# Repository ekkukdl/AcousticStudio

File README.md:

# Acoustic Control Studio

2026-10-08 T6 단면 클릭·드래그, 선택/전체 제어점 XYZ 이동, 비동기 궤적 이송과 최신 프레임 큐를 추가했습니다.
`구성 → 제어점`에서 이동 대상·단면·간격을 선택하며, 느린 계산에서는 이전 waypoint를 완료한 뒤 진행합니다.
[사용법·검증·현재 PC 성능](docs/ultraino_t6_result.md)을 확인하세요. 실제 터널 부양·이송 검증은 남아 있습니다.

현재 개발 저장소는 **[ekkukdl/AcousticStudio](https://github.com/ekkukdl/AcousticStudio)** 하나로 통합했습니다. 2026-10-07 기준 `AcousticStudio_ver2`의 코드, 구상도·PCB·Creo 자료 및 로컬 수정 내용을 반영했으며 두 저장소의 커밋 이력을 보존했습니다.

화면은 **보기 → UI → 클래식 / 모던**에서 선택합니다. 두 화면 모두 상단 **보드** 메뉴를 사용합니다. 설계 자료는 [구상도 시작 안내](구상도/START_HERE.md), 최신 32채널 PCB는 [제작 자료 안내](구상도/outputs/panel_8faces_32ch_R1/README.md)를 참고하세요. 통합 범위와 검증 기록은 [저장소 통합 기록](docs/repository_consolidation.md)에 있습니다.

Ultraino 기능 이식은 [작업 계획](docs/ultraino_migration_plan.md)을 기준으로 진행합니다. 현재 대상은 **Creo R2의 8면·8기판·기판당 32송신기, 총 256채널**이며 터널 축은 Z입니다. 기존 배열 좌표와 개발 환경을 재사용하는 범위 및 단계별 완료 조건을 정리했습니다. [입력·환경 점검 결과](docs/ultraino_migration_audit.json)는 현재 로컬 설치 상태의 기록입니다.

Acoustic Control Studio는 초음파 부상(Ultrasonic Levitation) 및 역장 제어(Acoustic Field Control) 연구를 위한 **통합 3D 시뮬레이션 및 하드웨어 제어 소프트웨어**입니다.
이 프로그램은 사용자가 직관적인 3D UI를 통해 센서 배열을 설계하고, 타겟의 위치를 조작하며, 실시간으로 위상(Phase)을 계산하여 하드웨어 보드(아두이노, FPGA 등)로 직접 전송할 수 있는 All-in-One 플랫폼을 제공합니다.

---

## 주요 기능 (Features)
- **3D 대화형 인터페이스 (Interactive 3D UI)**: PyVista 및 PySide6를 기반으로 한 3D 뷰어 제공.
- **다양한 배열 생성**: 터널형, 평면형, 반구형 등 복잡한 센서 배열(Array) 자동 생성 지원.
- **이기종 센서 하이브리드 지원**: 일반 10mm/16mm 초음파 센서와 고출력 랑주뱅(Langevin) 진동자의 혼합 시뮬레이션 지원.
- **실시간 위상 연산 (Real-time Phase Calculation)**: Twin Trap, Vortex Trap 등의 알고리즘을 적용하여 타겟 이동 시 위상을 즉각 재계산하고 색상으로 시각화.
- **하드웨어 연동 (USB Serial)**: 계산된 위상 데이터를 Byte 형식으로 변환하여 실시간으로 외부 제어 보드로 전송.

---

## 사전 설정 및 설치 가이드 (Prerequisites & Installation)

Creo 배열은 `구성 → 배열 형태 → Creo 8면 터널 · 8기판 × 32채널`을 선택하고 `배열 3D 렌더링 생성`으로 추가합니다. 기존 CAD 좌표를 읽으므로 일반 Grid/Spacing 값은 적용되지 않습니다. 위치·회전은 배열 전체에 적용되며, PCB 8개와 프레임 링 2개는 간략 형상으로 표시합니다. [구현 및 검증 기록](docs/ultraino_t1_result.md)을 참고하세요.

`음장 → 공통 음향 모델`에서 무지향, Ultraino sinc, 원형 피스톤을 선택합니다. 기본 개구는 미확정이며 CAD 외경에서 추정하지 않습니다. 방향성 모델에는 유효 음향 개구 반경이 필요하고, 음압은 미보정 상대값입니다. 설정을 바꾼 뒤 위상을 다시 계산하세요. [T2 결과 및 다음 작업](docs/ultraino_t2_result.md)에 데이터 계약과 검증 범위를 정리했습니다.

위상을 계산한 뒤 `음장 → 고정 위상 방사력·복원성 분석`에서 입자 물성, 중력, 평가 범위와 미분 간격을 입력합니다. 현재 송신을 고정한 XYZ 힘·퍼텐셜·복원 곡선과 전체 3×3 복원행렬을 확인하고 분석 JSON을 저장할 수 있습니다. 기본 물성은 예시이며 음압 미보정 상태의 힘은 N* 가정값입니다. 실제 중력 평형·부양 판정은 보류합니다. [T3 결과](docs/ultraino_t3_result.md)를 참고하세요.

다중 제어점을 활성화하고 `음장 → 다중 트랩 설계 (Kinoforms)`를 엽니다. 각 점에 Focus/Twin/Standing Wave, 상대 목표 음압 가중치와 세계 좌표 방향을 지정해 함께 계산합니다. 송신기 이득은 고정하고 위상만 조절하며, 반복 잔차·가중 음압 균일도를 확인한 뒤 `선택 트랩의 고정 위상 분석`으로 T3 복원 부호를 검사할 수 있습니다. `현재 배열에 위상 적용`과 `설계 JSON 저장`을 지원합니다. 음압 균일도는 부양 성공률이 아닙니다. [T4 사용·검증 및 T5 인계](docs/ultraino_t4_result.md)에 재현 방법을 정리했습니다.

`보드 → 채널 보정·맵 및 OFF 프레임…`에서 SW 채널별 위상 오프셋·고정 상대 이득·활성 상태와 후보 채널 맵을 편집하고 JSON/프로젝트로 저장합니다. 보정·맵·양자화·OFF는 실시간 송신과 궤적 내보내기에서 공통 사용합니다. 지원 프로파일의 OFF32와 위상0을 구분하며 Legacy OFF는 거절합니다. 실제 COM 없이 1채널/전체 OFF 프레임을 파일로 확인할 수 있습니다. [T5 사용·검증·T6 인계](docs/ultraino_t5_result.md)를 참고하세요. 실제 펌웨어·배선·파형 검증과 절대 음압 보정은 남아 있습니다.

상단 연산 모드에서 `PyTorch/CUDA: 선택 시 준비`를 선택하면 필요한 CUDA 패키지를 다운로드·확인한 뒤 그 모드를 적용합니다. `도구 → 라이브러리 관리자`의 `PyTorch/CUDA 사용` 체크도 같은 흐름입니다. 첫 준비는 수 GB 다운로드가 필요하며 이후 선택은 바로 전환합니다. 취소·실패는 이전 모드를 유지합니다. [선택 항목 적용 안내](docs/cuda_optional_selection.md)를 참고하세요. 다중 트랩은 복소 행렬 곱만 선택 엔진을 사용하며 작은 문제의 GPU 계산은 복사 비용 때문에 CPU보다 느릴 수 있습니다. [기존 원인·측정 기록](docs/multitrap_cuda_diagnosis.md)을 함께 확인할 수 있습니다.

현재 로컬 개발 환경은 Python 3.13.9이며, 확인한 인터프리터와 의존성은 [이식 계획의 환경 안내](docs/ultraino_migration_plan.md)에 있습니다. 기존 환경을 먼저 확인하고 재사용하세요. 기본 `py`가 선택하는 Python과 앱용 환경은 다를 수 있습니다. 필수 의존성 10개는 `requirements.txt`와 공통 설치 카탈로그에 일치하며, 확인한 버전은 [requirements-tested.txt](requirements-tested.txt)에 기록했습니다. T2는 이미 설치된 SciPy를 재사용했습니다. 아래 신규 설치 예시는 새 머신에 필요한 경우에 사용합니다.

### 1. Python 가상 환경 설정 (선택 사항이나 권장)
```bash
python -m venv venv
# Windows
venv\Scripts\activate
# Mac/Linux
source venv/bin/activate
```

### 2. 필수 라이브러리 설치
프로젝트 루트 폴더에 포함된 `requirements.txt`를 사용하여 의존성 패키지를 한 번에 설치합니다.
```bash
pip install -r requirements.txt
```
**[설치되는 주요 패키지]**
- `PySide6`: GUI 프레임워크
- `pyvista`, `pyvistaqt`, `vtk`: 3D 렌더링 및 기하학 연산 엔진
- `numpy`: 고속 배열 및 위상 수학 연산
- `pyserial`: 하드웨어(USB) 시리얼 통신 모듈

### 3. 프로그램 실행
모든 설치가 완료되었다면, 최상단 경로에서 아래 명령어를 통해 메인 창을 띄울 수 있습니다.
```bash
python main.py
```

---

## 디렉터리 구조 (Directory Structure)
- `src/acousticstudio/`: 애플리케이션의 핵심 소스 코드 (`app.py`, `app_backup.py` 등)
- `main.py`: 프로그램 실행 진입점 (Entry point)
- `docs/`: AI 에이전트 가이드라인 및 프로젝트 진행 상태(`project_status.txt`)가 기록된 문서 폴더
- `archive/temp_scripts/`: 개발 과정에서 생성된 임시 수정 스크립트(수동 코드 인젝션 파일) 모음 보관소
- `requirements.txt`: 의존성 패키지 목록

---

## 주의 사항 (Notes)
- **그래픽 드라이버**: 3D 렌더링 엔진인 VTK/PyVista를 사용하므로, 그래픽 드라이버(OpenGL 호환)가 정상적으로 설치된 환경에서 실행해야 튕김 현상이 발생하지 않습니다.
- **AI 작업 지침**: GPT/Codex를 포함한 코딩 에이전트는 [AGENTS.md](AGENTS.md)의 작업·백업·검증 규칙을 따릅니다. 기존 `GEMINI.md`도 이 공통 지침을 안내합니다. 스킬 점검 내역은 [docs/skill_audit.md](docs/skill_audit.md)에 있습니다.

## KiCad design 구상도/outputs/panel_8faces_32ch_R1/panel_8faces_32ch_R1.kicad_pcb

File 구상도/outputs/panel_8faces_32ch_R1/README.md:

# 8면 터널용 32채널 PCB R1 — KiCad 10

기존 16채널 회로와 배선을 두 전기적 뱅크로 재사용해, 4열 × 8행의 트랜스듀서를 한 장에 배치한 새 설계입니다. 같은 PCB 8장으로 총 256채널을 구성합니다. 기존 설계 파일은 수정하지 않았습니다. 실제 PCB 발주·조립·구동은 수행하지 않았습니다.

## 파일 열기

`panel_8faces_32ch_R1.kicad_pro`를 KiCad 10에서 엽니다. 회로도와 PCB, 프로젝트 로컬 심벌/풋프린트 및 모델이 함께 들어 있습니다. 회로도는 620 × 460 mm 사용자 용지의 단일 시트입니다.

## 이번 시제품의 치수

| 항목 | R1 값 | 의미 |
|---|---:|---|
| PCB | 84 × 224 × 1.6 mm | 2층, 면마다 1장 |
| 발진면 맞은편 거리 | 210 mm | 기존 300 mm에서 축소한 시작점 |
| PCB 앞면의 중심까지 거리 | 117.5 mm | 발진면 거리 + 가정한 소자 높이 12.5 mm |
| 트랜스듀서 | 4 × 8, 지름 16 mm | 기존 풋프린트 사용, 정확한 구매품 확인 필요 |
| 열 중심 간격 | 18 / 22 / 18 mm | 두 기존 배선 셀 사이에 4 mm를 더 확보 |
| 행 중심 간격 | 20 mm | 기존과 동일 |
| 위·아래 고정 여백 | 각각 22 mm | 부품·배선·동박 채움 없는 영역 |
| 고정 구멍 | 4개, 지름 3.2 mm NPTH | (6,11), (78,11), (6,213), (78,213) mm |
| 인접 PCB 앞면 모서리 거리 | 약 12.325 mm | 광학 유효 개구 폭이나 시야각을 뜻하지 않음 |

기판 내부 슬롯은 없습니다. 기판 사이 틈을 남기는 정팔각형 터널 배치이며 외부 카메라와 회전 프레임 자체는 이번 설계 범위 밖입니다. 물체 전체가 보이는 조건은 유지해야 하지만 물체 크기와 촬영 위치가 없어 아직 증명되지 않았습니다.

200 mm가 절대 기준은 아니므로, 기존 셀 배선 유지와 틈 확보를 위해 210 mm를 선택했습니다. 같은 84 mm PCB를 발진면 거리 200 mm로 배치하면 앞면 모서리 거리는 약 8.498 mm로 줄어듭니다. 두 경우 모두 소자 외피는 단순 모델상 충돌하지 않지만 카메라 시야·음향 부상 성능은 별도 검증이 필요합니다. 기판 뒤 부품, 케이블, 프레임은 틈을 더 가릴 수 있습니다.

`parameters.json`은 현재 치수 기록입니다. 생성 스크립트는 보드 폭·길이와 발진면 거리를 조정할 수 있으나 열·행 간격, 소자 높이, 고정 여백 변경을 임의로 자동 배선하지 않습니다. 변경 후 네이티브 파일·간섭·ERC/DRC·제조 파일을 다시 검증해야 합니다. JSON 수치만 바꿔 기존 Gerber를 그대로 사용할 수 없습니다.

## 전기 구성과 연결

32채널을 16채널 A/B 뱅크로 나눕니다. 뱅크 사이에서 PCB 내부로 연결된 공통 전원망은 GND뿐입니다. +5V_A/B, DRV_VDD_A/B, SHIFT/LATCH/ARM_A/B는 각각 외부에서 공급합니다. 같은 공급원이나 클록을 쓰려면 외부 분배가 필요합니다. 한쪽 헤더만 연결하면 다른 뱅크가 자동 동작하지 않습니다.

| 핀 | J1: BANK A 신호 | J2: BANK B 신호 |
|---:|---|---|
|1|GND|GND|
|2|+5V_A|+5V_B|
|3|DATA_A0|DATA_B0|
|4|GND|GND|
|5|DATA_A1|DATA_B1|
|6|GND|GND|
|7|SHIFT_PIN_A|SHIFT_PIN_B|
|8|LATCH_PIN_A|LATCH_PIN_B|
|9|ARM_A|ARM_B|
|10|GND|GND|

J3(A), J4(B) 전원 헤더는 1=DRV_VDD, 2=GND, 3=+5V입니다. 실크와 패드 번호를 기준으로 확인하고 커넥터 뒷면 시점의 좌우를 추측하지 마세요. +5V는 5 V 로직 공급이며 TC4427A의 드라이버 전원 허용 범위는 4.5–18 V입니다. 실제 트랜스듀서의 연속 구동 정격 확인 전 드라이버 전압을 확정하지 않습니다.

ARM 기본 풀다운 → MMBT3904 OFF → 74HCT595 /OE 풀업으로 출력 비활성화합니다. 입력 풀다운으로 TC4427A 입력의 부유를 방지합니다. 전원 안정 후 ARM 비활성 상태에서 4개의 데이터 라인에 값을 시프트하고 래치한 다음 ARM을 활성화하는 순서를 사용합니다. 외부 FPGA와 헤더 배선은 이번에 변경하지 않았습니다.

T1…T32는 행 우선 순서입니다. QA…QH 출력 기준 `channel_map.csv`와 전체 256개 위치 `array_positions_256.json`을 제공합니다. `physical_to_software_channel_map.json`은 문서화한 DATA 순서에 대응하는 후보이며 FPGA의 실제 시프트 비트 방향과 헤더 배선을 확인하기 전 기존 프로그램에 바로 적용하지 않습니다.

## 제작·조립 자료

- `Gerber_R1_PCB_only.zip`: 동박·마스크·실크·페이스트·외곽, PTH/NPTH 드릴 및 Gerber job. PCB 1장 패턴이며 8장 주문 수량은 별도 지정합니다.
- `BOM_ALL.csv`, `BOM_SMT.csv`, `BOM_THT.csv`: 1장 및 8장 수량, 후보 MPN. 1장당 SMT 110개와 THT 38개입니다. M3 고정 나사·프레임·케이블은 포함하지 않습니다.
- `PnP_SMT_KiCad.csv`: KiCad 원본 좌표, mm, Bottom, X 양수/Y 음수. 임의 미러 변환을 하지 않았습니다. 업체의 바닥면 좌표 규약과 반드시 맞춰야 합니다.
- `THT_Placement.csv`: 트랜스듀서·헤더·전해콘덴서 수동 조립 위치. TX 패드1=출력/패드2=GND, 전해콘덴서 패드1=양극입니다.
- `mechanical/panel_board_only.step`: 실제 PCB 외곽·고정 구멍의 STEP. 부품 및 외부 프레임 미포함.
- `mechanical/tunnel_envelope.scad`: 8면 PCB/소자 외피의 치수 모델. 고정 구조 설계용 완성 프레임이 아닙니다.
- `geometry_preview.png`, `assembly_preview.png`, `pcb_top.png`, `pcb_bottom.png`, `schematic_preview.png`: 배치·실제 회로도·배선 미리보기.

PCB 제안 사양은 FR-4, 2층, 1.6 mm, 1 oz 동박이며 제작업체의 실제 공정 사양을 확인해야 합니다. 업체 패널라이징, 리플로우 캐리어, 스텐실 여백, 부품 대체 선정은 이번 패키지에 포함하지 않습니다. THT 트랜스듀서는 안쪽 F면, 구동 부품은 바깥쪽 B면에 배치합니다.

## 검증과 남은 사항

KiCad 10.0.6 ERC 0, DRC 위반 0, 미연결 0, 회로도/PCB 불일치 0. 별도 검증에서 전기 패드 468개(연결 432개/명시 NC 36개), 32개 출력 경로, 256채널 맵, SMT 좌표와 고정 여백을 확인했습니다. 원본 PCB의 SHA-256도 유지되었습니다. GND 비아 92개를 추가했습니다.

기존 프로젝트의 5개 DRC ignore 설정과 ERC ignore 설정은 유지되며 검증 범위는 `DESIGN_REVIEW.md`에 기록했습니다. 제조업체 DFM, 실제 전류·온도·신호 파형·음향 부상과 전체 물체 촬영은 검증되지 않았습니다. 자동 EMC 검토의 귀환 경로 및 외부 케이블 경고가 남아 있어 측정과 필요시 배선 수정이 필요합니다. 자세한 판단과 근거는 `DESIGN_REVIEW.md`, 기계 판정은 `geometry_summary.json`, 원시 검사 결과는 `analysis/`에 있습니다.

## 재생성

프로젝트 루트에서 `구상도/scratch/build_panel32_r1.py`와 `stitch_panel32_r1.py`, `verify_panel32_r1.py`를 KiCad 내장 Python으로 실행합니다. `export_panel32_r1.py`, `render_panel32_r1.py`, `package_panel32_r1.py`는 시스템 Python을 사용합니다. 검증은 ERC/DRC와 XML netlist 내보내기 뒤 수행합니다. 렌더에는 로컬 resvg-py/Pillow, 치수 미리보기에는 numpy/matplotlib이 필요합니다. 생성은 기존 16채널 소스 셀을 읽으므로 소스 폴더가 필요하며 새 설계를 편집한 뒤 생성 스크립트를 다시 실행하면 R1 편집 내용이 덮어써집니다.

## 색상 및 외부 프레임 포함 Creo 모델 R2

[전체 조립체](mechanical/creo32_frame_R2/native/tunnel8_32_r2.asm)는 진녹색 PCB 8장과 회색 상하 팔각 링 2개를 포함합니다. 전체 외형 265×265×224 mm, 기존 PCB 고정 구멍에 맞춘 M3 체결 구멍 및 촬영용 면간 틈을 유지했습니다. [Creo R2 사용안내](mechanical/creo32_frame_R2/사용안내.md)에 치수·파일·검증 범위가 있으며, [모델 ZIP](mechanical/creo32_frame_R2/Creo32_frame_R2_models.zip)에 모든 참조 단품을 포함했습니다. 기판 조립체는 `panel32_r2.asm`, 기판 단품은 `pcb32_r2.prt`, 링 단품은 `ring8_32_r2.prt`입니다. 이전 R1 모델은 보존했습니다.

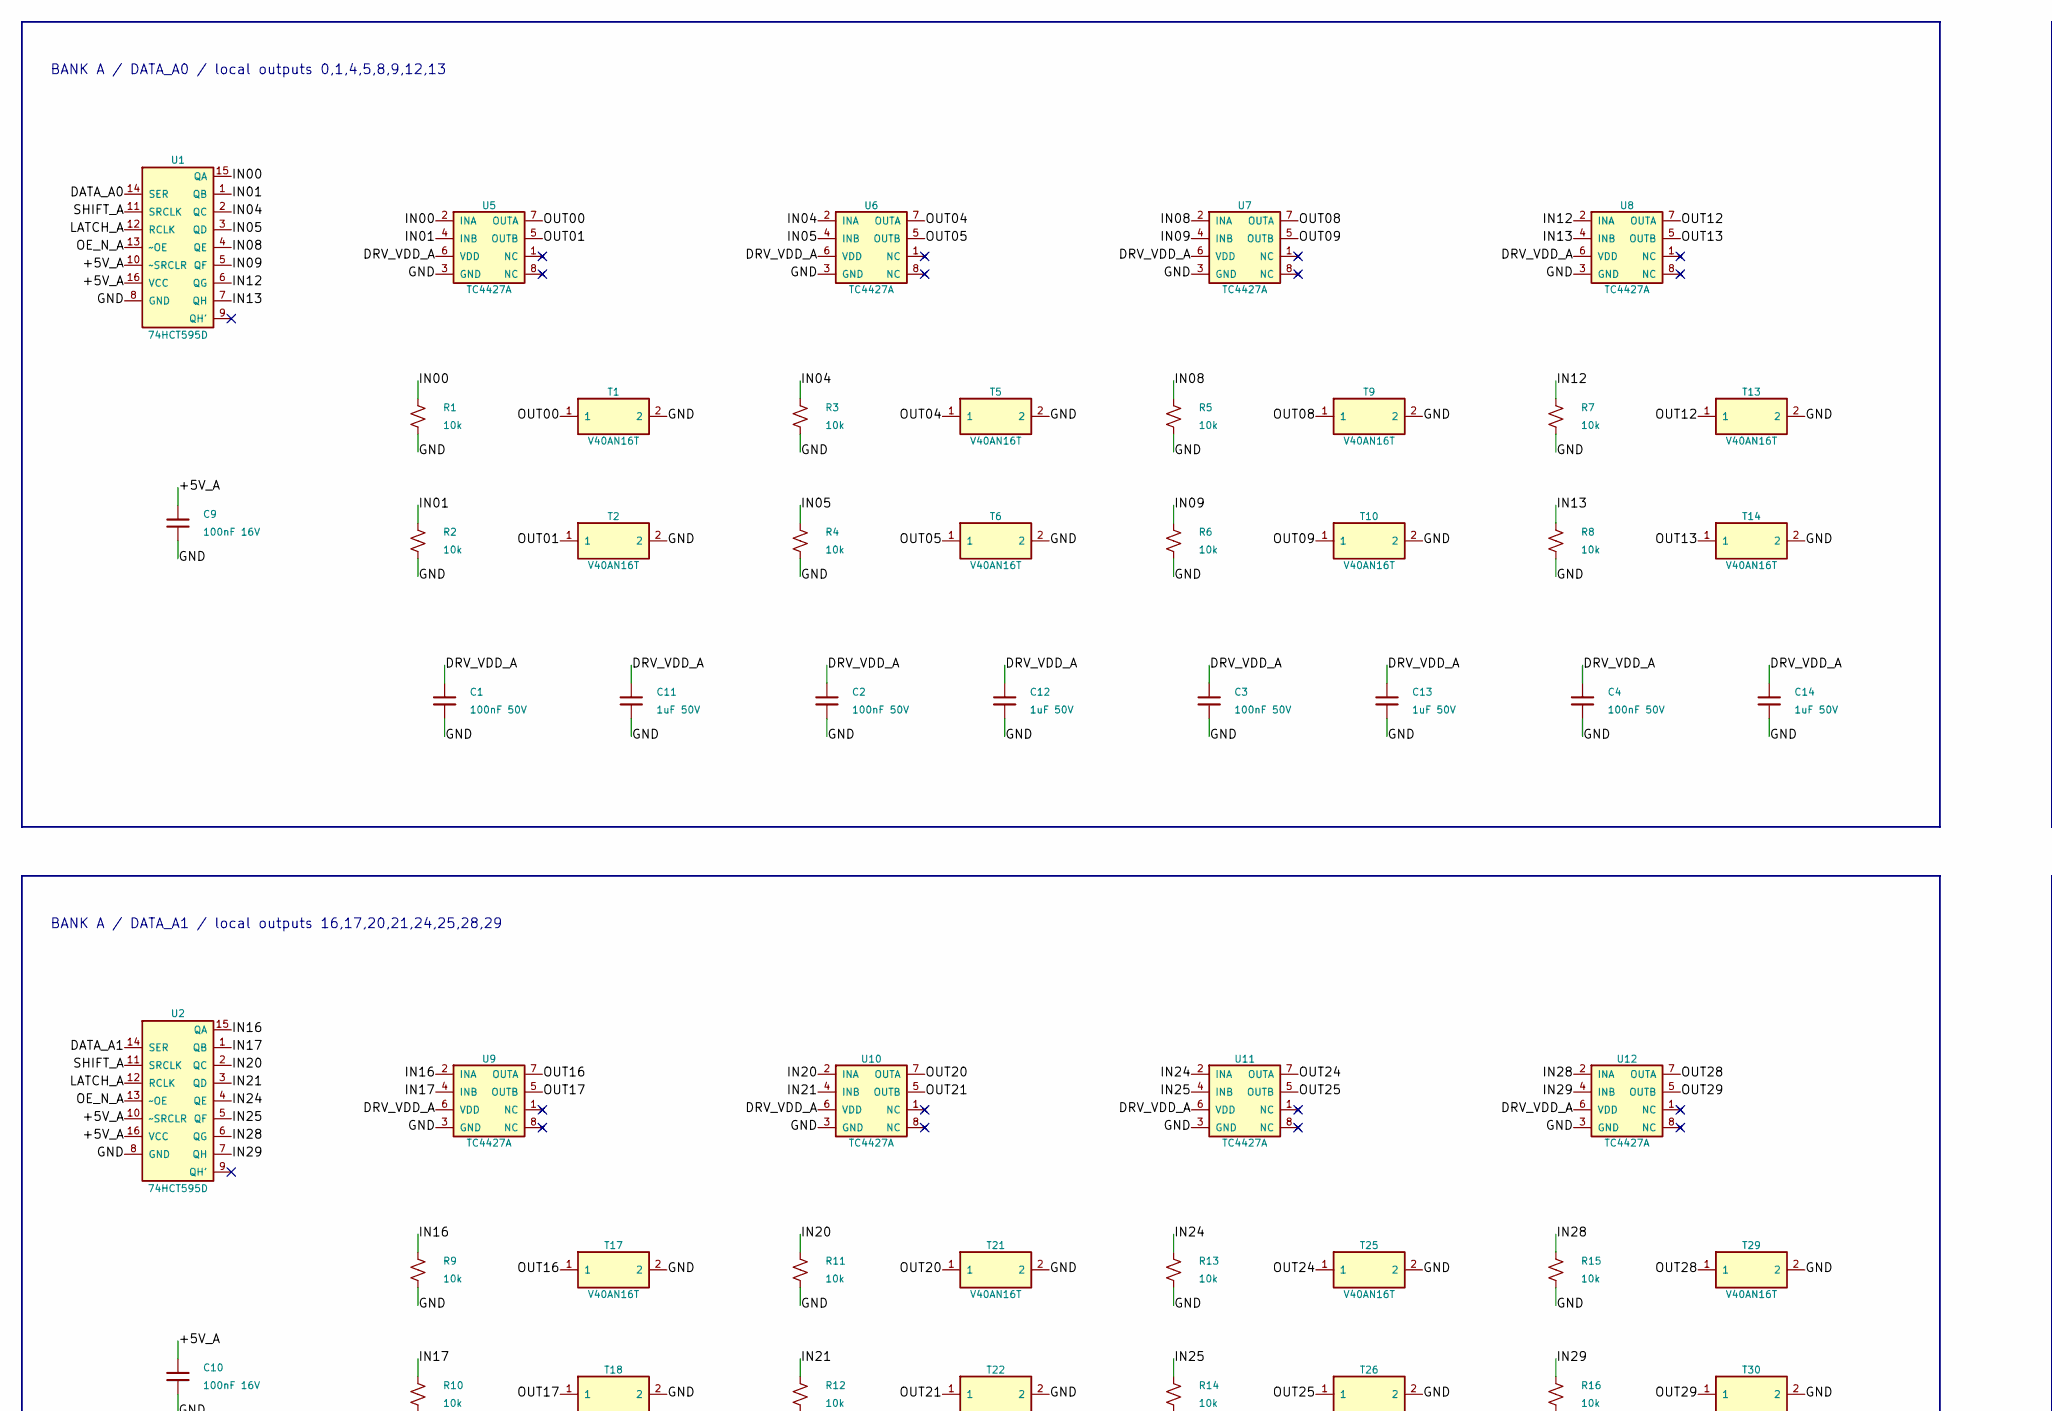
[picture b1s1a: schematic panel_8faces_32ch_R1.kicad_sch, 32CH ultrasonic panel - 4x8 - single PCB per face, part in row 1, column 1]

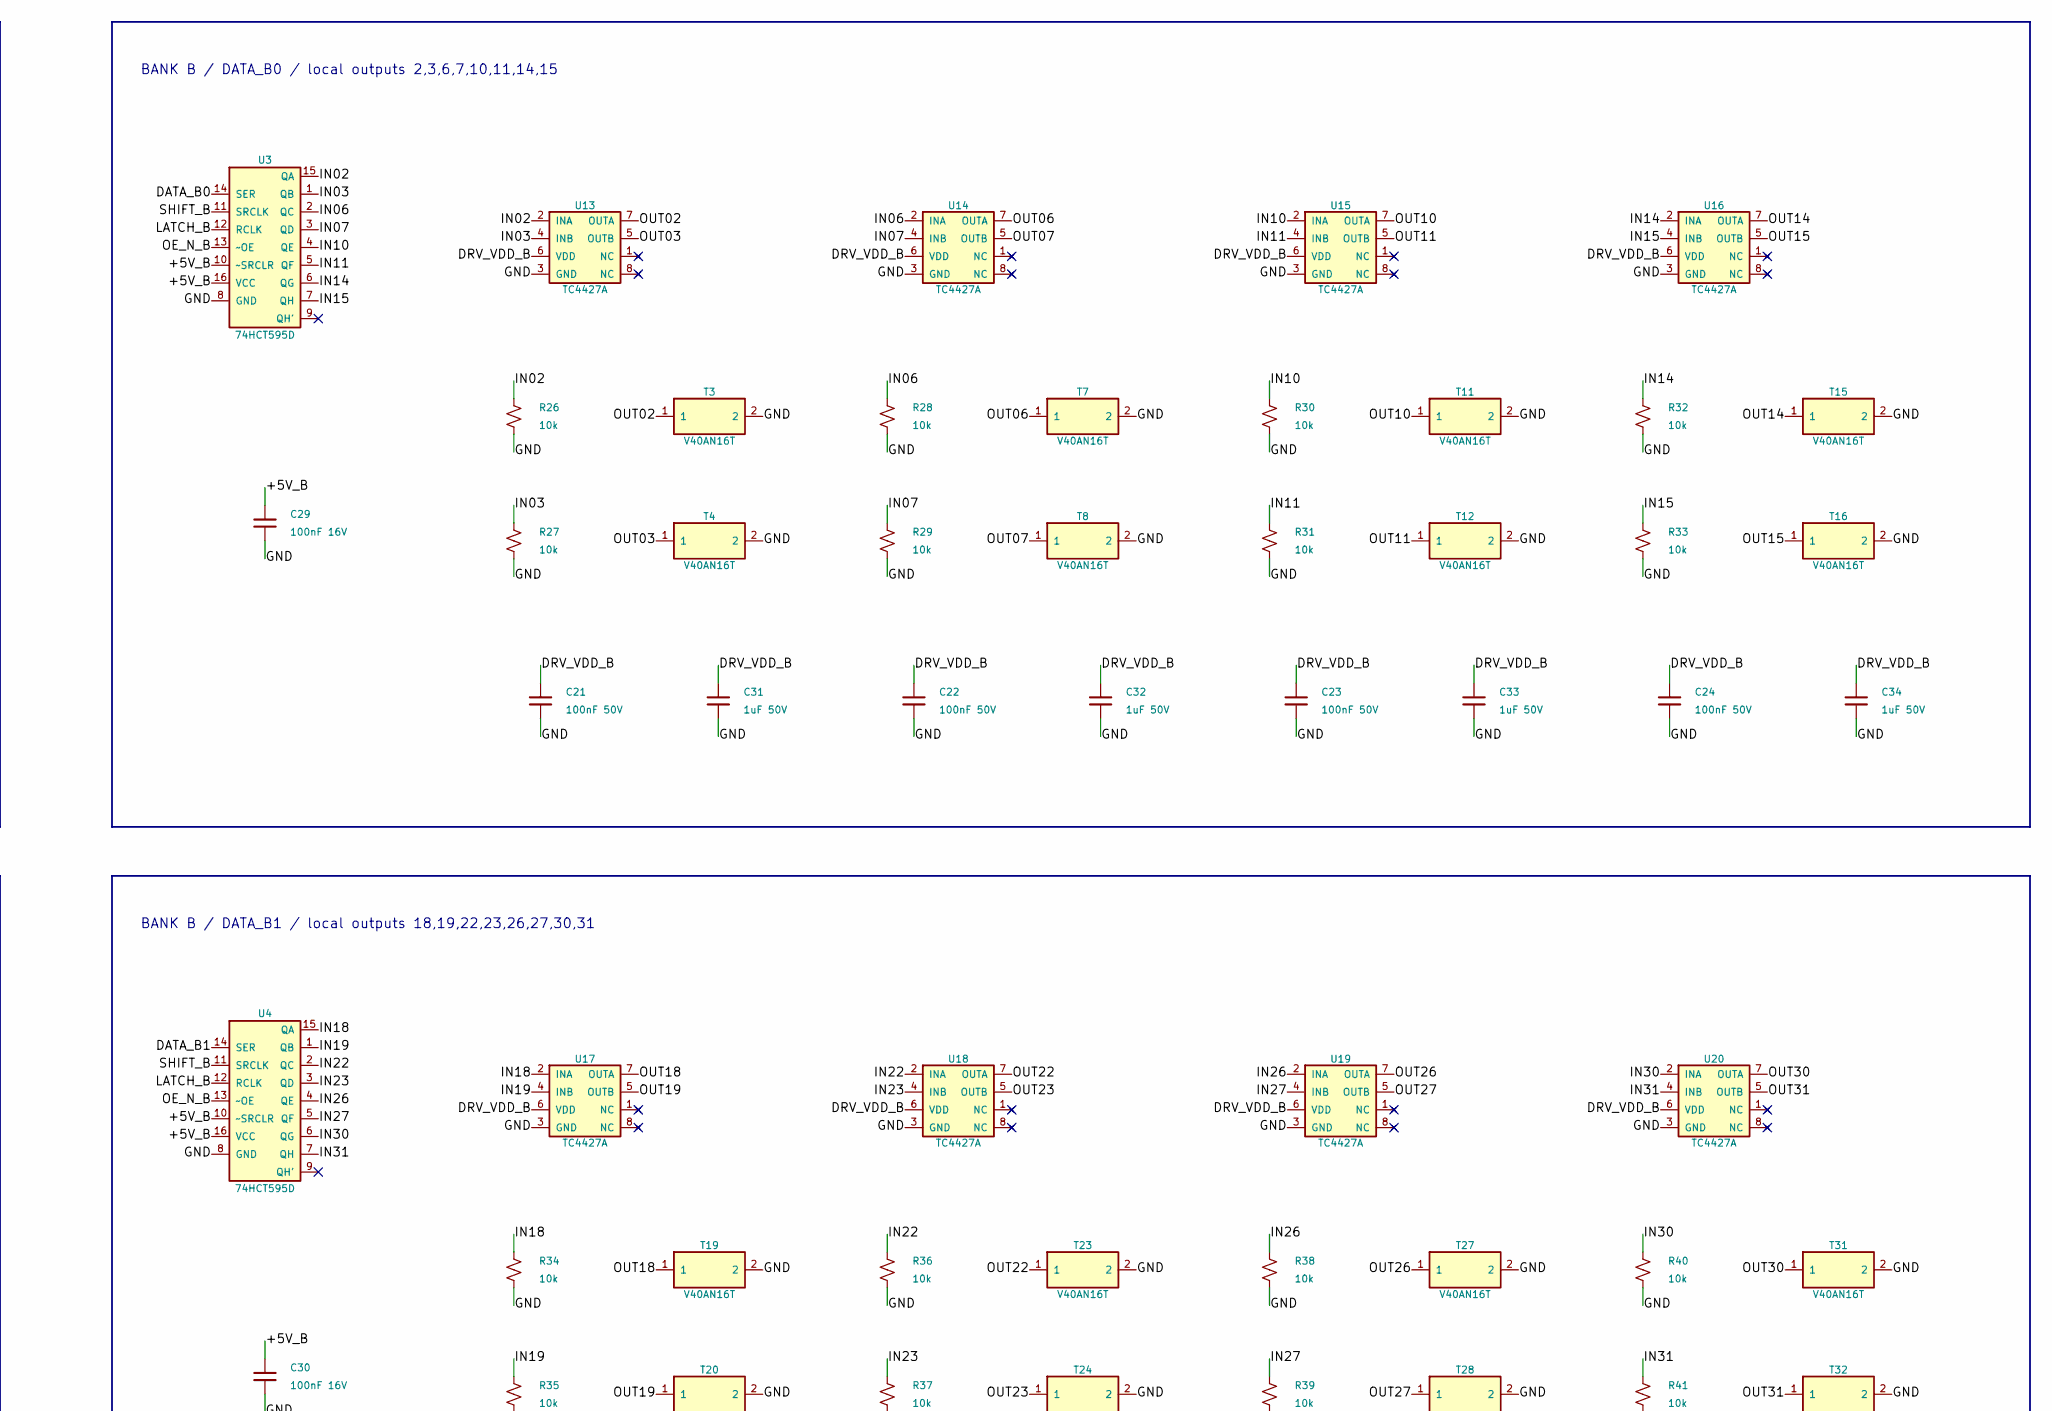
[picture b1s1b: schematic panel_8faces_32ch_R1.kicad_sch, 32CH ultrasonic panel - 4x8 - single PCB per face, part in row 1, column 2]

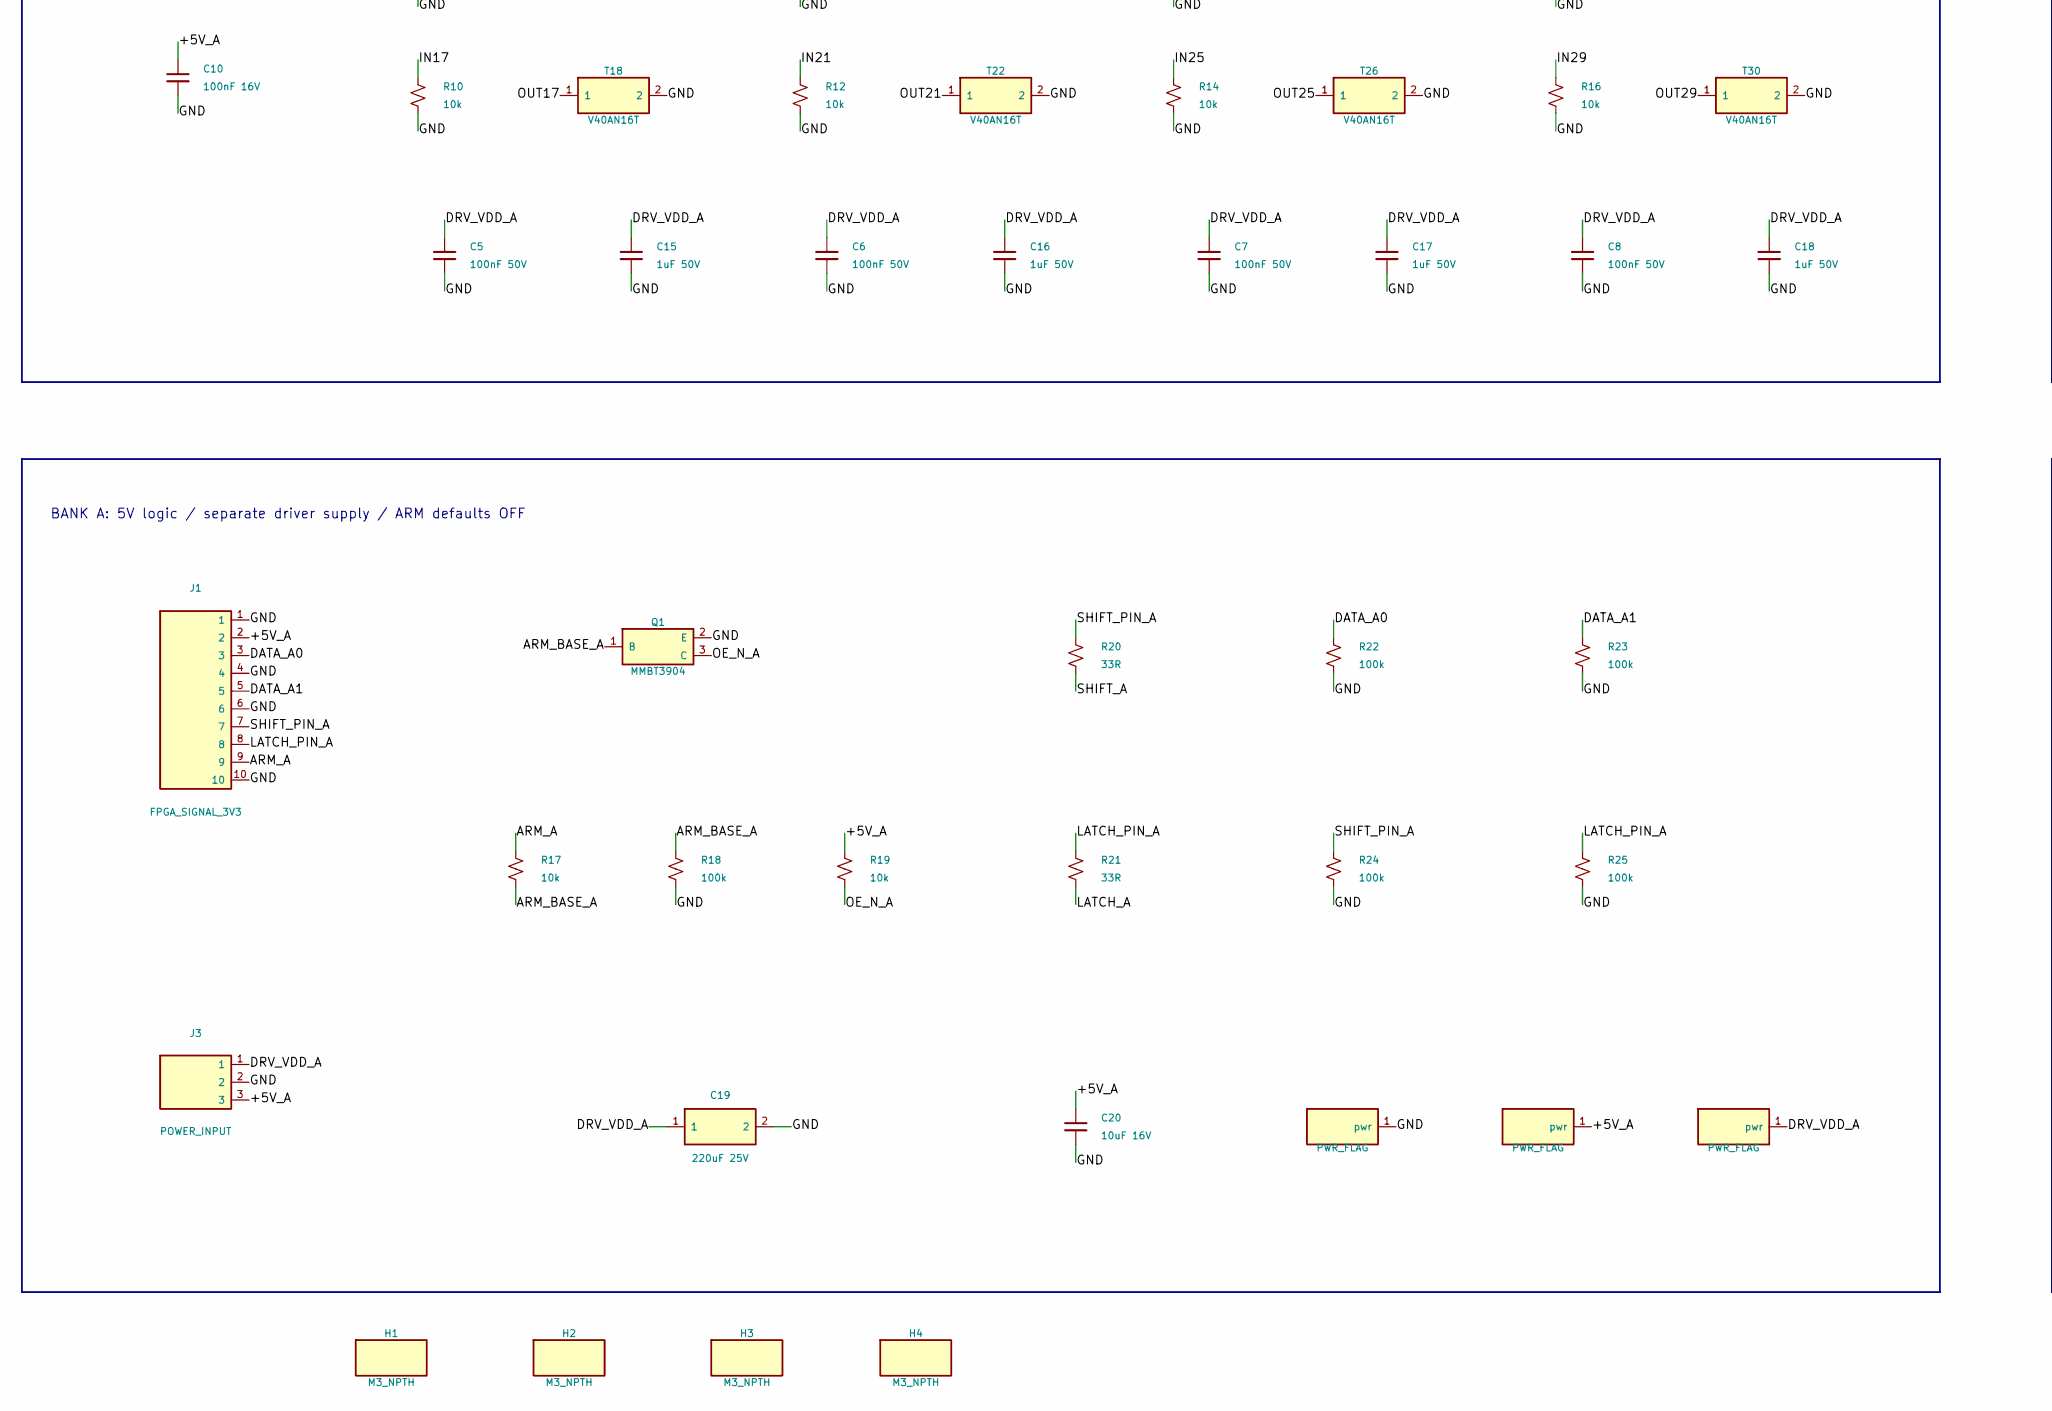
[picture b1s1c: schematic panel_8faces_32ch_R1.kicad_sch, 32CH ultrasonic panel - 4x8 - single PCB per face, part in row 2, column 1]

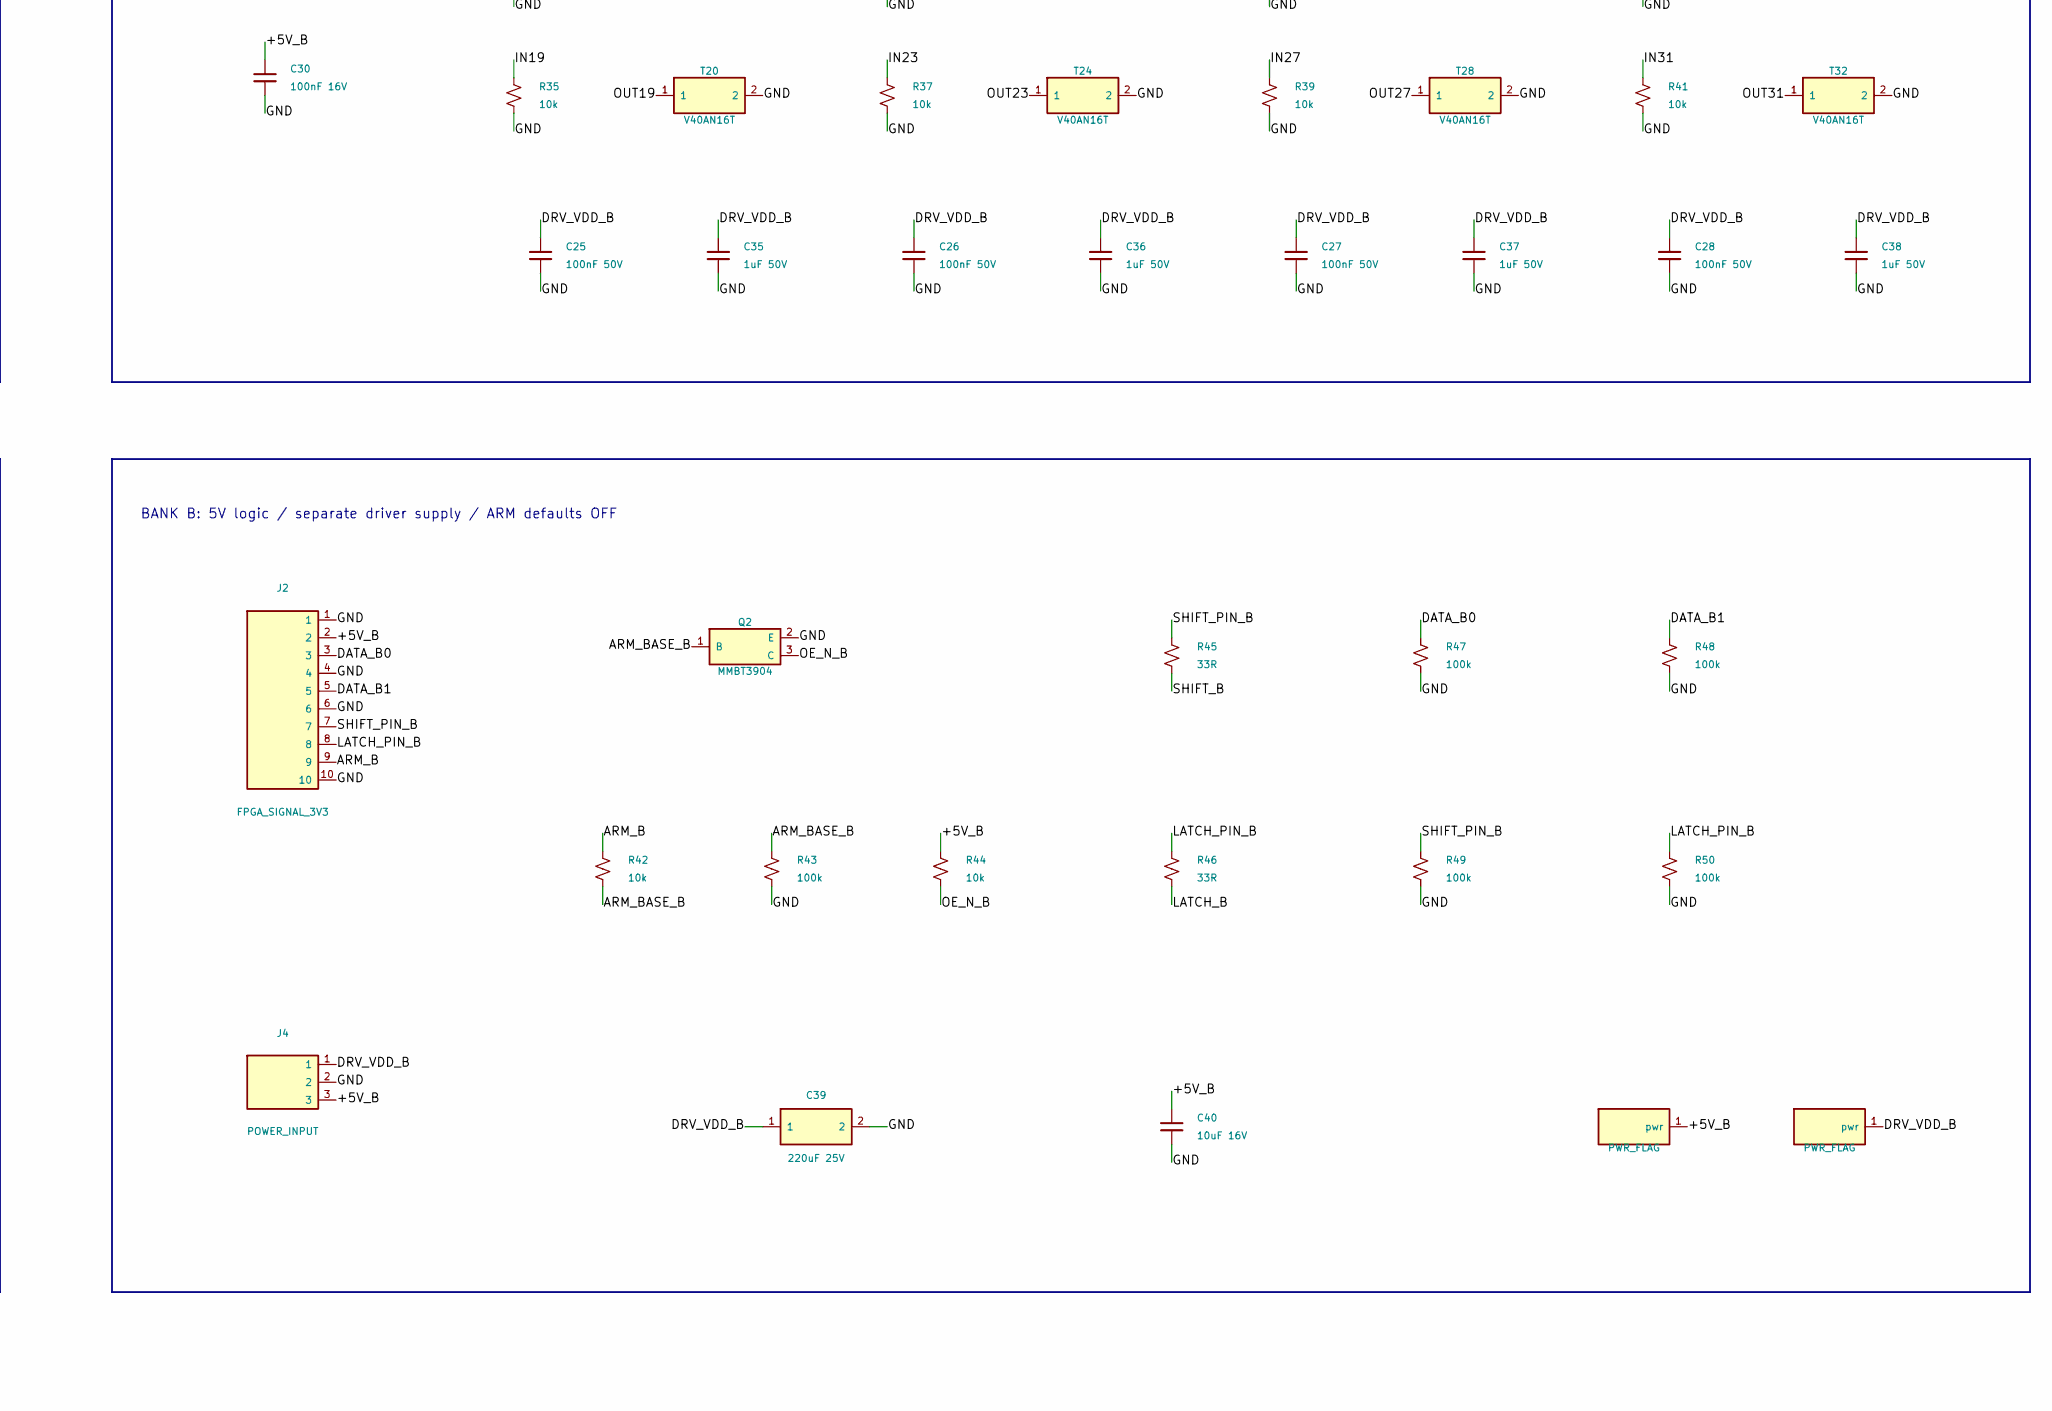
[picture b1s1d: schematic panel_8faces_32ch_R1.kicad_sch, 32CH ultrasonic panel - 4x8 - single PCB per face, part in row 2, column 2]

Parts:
C1, C2, C3, C4, C5, C6, C7, C8, C21, C22, C23, C24, C25, C26, C27, C28: 100nF 50V; C0805; MPN CC0805KRX7R9BB104
C9, C10, C29, C30: 100nF 16V; C0805; MPN CC0805KRX7R9BB104
C11, C12, C13, C14, C15, C16, C17, C18, C31, C32, C33, C34, C35, C36, C37, C38: 1uF 50V; C0805; MPN TCC0805X7R105K500DT
C19, C39: 220uF 25V; CP_Radial_D6.3_P2.5; MPN 25YXJ220M6.3X11
C20, C40: 10uF 16V; C0805; MPN GRM21BR61E106KA73L
H1, H2, H3, H4: M3_NPTH; Mount_M3
J1, J2: FPGA_SIGNAL_3V3; Header2x05
J3, J4: POWER_INPUT; Header1x03
Q1, Q2: MMBT3904; SOT23; MPN MMBT3904,215
R1, R2, R3, R4, R5, R6, R7, R8, R9, R10, R11, R12, R13, R14, R15, R16, R17, R19, R26, R27, R28, R29, R30, R31, R32, R33, R34, R35, R36, R37, R38, R39, R40, R41, R42, R44: 10k; R0805; MPN RC0805FR-0710KL
R18, R22, R23, R24, R25, R43, R47, R48, R49, R50: 100k; R0805; MPN RC0805FR-07100KL
R20, R21, R45, R46: 33R; R0805; MPN RC0805FR-0733RL
T1, T2, T3, T4, T5, T6, T7, T8, T9, T10, T11, T12, T13, T14, T15, T16, T17, T18, T19, T20, T21, T22, T23, T24, T25, T26, T27, T28, T29, T30, T31, T32: V40AN16T; V40AN16T_P10
U1, U2, U3, U4: 74HCT595D; SOIC16; MPN 74HCT595D,118
U5, U6, U7, U8, U9, U10, U11, U12, U13, U14, U15, U16, U17, U18, U19, U20: TC4427A; SOIC8; MPN TC4427ACOA713

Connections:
/+5V_A: C9.1, C10.1, C20.1, J1.2, J3.3, R19.1, U1.10 (~SRCLR), U1.16 (VCC), U2.10 (~SRCLR), U2.16 (VCC)
/+5V_B: C29.1, C30.1, C40.1, J2.2, J4.3, R44.1, U3.10 (~SRCLR), U3.16 (VCC), U4.10 (~SRCLR), U4.16 (VCC)
/ARM_A: J1.9, R17.1
/ARM_B: J2.9, R42.1
/ARM_BASE_A: Q1.1 (B), R17.2, R18.1
/ARM_BASE_B: Q2.1 (B), R42.2, R43.1
/DATA_A0: J1.3, R22.1, U1.14 (SER)
/DATA_A1: J1.5, R23.1, U2.14 (SER)
/DATA_B0: J2.3, R47.1, U3.14 (SER)
/DATA_B1: J2.5, R48.1, U4.14 (SER)
/DRV_VDD_A: C1.1, C2.1, C3.1, C4.1, C5.1, C6.1, C7.1, C8.1, C11.1, C12.1, C13.1, C14.1, C15.1, C16.1, C17.1, C18.1, C19.1, J3.1, U5.6 (VDD), U6.6 (VDD), U7.6 (VDD), U8.6 (VDD), U9.6 (VDD), U10.6 (VDD), U11.6 (VDD), U12.6 (VDD)
/DRV_VDD_B: C21.1, C22.1, C23.1, C24.1, C25.1, C26.1, C27.1, C28.1, C31.1, C32.1, C33.1, C34.1, C35.1, C36.1, C37.1, C38.1, C39.1, J4.1, U13.6 (VDD), U14.6 (VDD), U15.6 (VDD), U16.6 (VDD), U17.6 (VDD), U18.6 (VDD), U19.6 (VDD), U20.6 (VDD)
/GND: C1.2, C2.2, C3.2, C4.2, C5.2, C6.2, C7.2, C8.2, C9.2, C10.2, C11.2, C12.2, C13.2, C14.2, C15.2, C16.2, C17.2, C18.2, C19.2, C20.2, C21.2, C22.2, C23.2, C24.2, C25.2, C26.2, C27.2, C28.2, C29.2, C30.2, C31.2, C32.2, C33.2, C34.2, C35.2, C36.2, C37.2, C38.2, C39.2, C40.2, J1.1, J1.4, J1.6, J1.10, J2.1, J2.4, J2.6, J2.10, J3.2, J4.2, Q1.2 (E), Q2.2 (E), R1.2, R2.2, R3.2, R4.2, R5.2, R6.2, R7.2, R8.2, R9.2, R10.2, R11.2, R12.2, R13.2, R14.2, R15.2, R16.2, R18.2, R22.2, R23.2, R24.2, R25.2, R26.2, R27.2, R28.2, R29.2, R30.2, R31.2, R32.2, R33.2, R34.2, R35.2, R36.2, R37.2, R38.2, R39.2, R40.2, R41.2, R43.2, R47.2, R48.2, R49.2, R50.2, T1.2, T2.2, T3.2, T4.2, T5.2, T6.2, T7.2, T8.2, T9.2, T10.2, T11.2, T12.2, T13.2, T14.2, T15.2, T16.2, T17.2, T18.2, T19.2, T20.2, T21.2, T22.2, T23.2, T24.2, T25.2, T26.2, T27.2, T28.2, T29.2, T30.2, T31.2, T32.2, U1.8 (GND), U2.8 (GND), U3.8 (GND), U4.8 (GND), U5.3 (GND), U6.3 (GND), U7.3 (GND), U8.3 (GND), U9.3 (GND), U10.3 (GND), U11.3 (GND), U12.3 (GND), U13.3 (GND), U14.3 (GND), U15.3 (GND), U16.3 (GND), U17.3 (GND), U18.3 (GND), U19.3 (GND), U20.3 (GND)
/IN00: R1.1, U1.15 (QA), U5.2 (INA)
/IN01: R2.1, U1.1 (QB), U5.4 (INB)
/IN02: R26.1, U3.15 (QA), U13.2 (INA)
/IN03: R27.1, U3.1 (QB), U13.4 (INB)
/IN04: R3.1, U1.2 (QC), U6.2 (INA)
/IN05: R4.1, U1.3 (QD), U6.4 (INB)
/IN06: R28.1, U3.2 (QC), U14.2 (INA)
/IN07: R29.1, U3.3 (QD), U14.4 (INB)
/IN08: R5.1, U1.4 (QE), U7.2 (INA)
/IN09: R6.1, U1.5 (QF), U7.4 (INB)
/IN10: R30.1, U3.4 (QE), U15.2 (INA)
/IN11: R31.1, U3.5 (QF), U15.4 (INB)
/IN12: R7.1, U1.6 (QG), U8.2 (INA)
/IN13: R8.1, U1.7 (QH), U8.4 (INB)
/IN14: R32.1, U3.6 (QG), U16.2 (INA)
/IN15: R33.1, U3.7 (QH), U16.4 (INB)
/IN16: R9.1, U2.15 (QA), U9.2 (INA)
/IN17: R10.1, U2.1 (QB), U9.4 (INB)
/IN18: R34.1, U4.15 (QA), U17.2 (INA)
/IN19: R35.1, U4.1 (QB), U17.4 (INB)
/IN20: R11.1, U2.2 (QC), U10.2 (INA)
/IN21: R12.1, U2.3 (QD), U10.4 (INB)
/IN22: R36.1, U4.2 (QC), U18.2 (INA)
/IN23: R37.1, U4.3 (QD), U18.4 (INB)
/IN24: R13.1, U2.4 (QE), U11.2 (INA)
/IN25: R14.1, U2.5 (QF), U11.4 (INB)
/IN26: R38.1, U4.4 (QE), U19.2 (INA)
/IN27: R39.1, U4.5 (QF), U19.4 (INB)
/IN28: R15.1, U2.6 (QG), U12.2 (INA)
/IN29: R16.1, U2.7 (QH), U12.4 (INB)
/IN30: R40.1, U4.6 (QG), U20.2 (INA)
/IN31: R41.1, U4.7 (QH), U20.4 (INB)
/LATCH_A: R21.2, U1.12 (RCLK), U2.12 (RCLK)
/LATCH_B: R46.2, U3.12 (RCLK), U4.12 (RCLK)
/LATCH_PIN_A: J1.8, R21.1, R25.1
/LATCH_PIN_B: J2.8, R46.1, R50.1
/OE_N_A: Q1.3 (C), R19.2, U1.13 (~OE), U2.13 (~OE)
/OE_N_B: Q2.3 (C), R44.2, U3.13 (~OE), U4.13 (~OE)
/OUT00: T1.1, U5.7 (OUTA)
/OUT01: T2.1, U5.5 (OUTB)
/OUT02: T3.1, U13.7 (OUTA)
/OUT03: T4.1, U13.5 (OUTB)
/OUT04: T5.1, U6.7 (OUTA)
/OUT05: T6.1, U6.5 (OUTB)
/OUT06: T7.1, U14.7 (OUTA)
/OUT07: T8.1, U14.5 (OUTB)
/OUT08: T9.1, U7.7 (OUTA)
/OUT09: T10.1, U7.5 (OUTB)
/OUT10: T11.1, U15.7 (OUTA)
/OUT11: T12.1, U15.5 (OUTB)
/OUT12: T13.1, U8.7 (OUTA)
/OUT13: T14.1, U8.5 (OUTB)
/OUT14: T15.1, U16.7 (OUTA)
/OUT15: T16.1, U16.5 (OUTB)
/OUT16: T17.1, U9.7 (OUTA)
/OUT17: T18.1, U9.5 (OUTB)
/OUT18: T19.1, U17.7 (OUTA)
/OUT19: T20.1, U17.5 (OUTB)
/OUT20: T21.1, U10.7 (OUTA)
/OUT21: T22.1, U10.5 (OUTB)
/OUT22: T23.1, U18.7 (OUTA)
/OUT23: T24.1, U18.5 (OUTB)
/OUT24: T25.1, U11.7 (OUTA)
/OUT25: T26.1, U11.5 (OUTB)
/OUT26: T27.1, U19.7 (OUTA)
/OUT27: T28.1, U19.5 (OUTB)
/OUT28: T29.1, U12.7 (OUTA)
/OUT29: T30.1, U12.5 (OUTB)
/OUT30: T31.1, U20.7 (OUTA)
/OUT31: T32.1, U20.5 (OUTB)
/SHIFT_A: R20.2, U1.11 (SRCLK), U2.11 (SRCLK)
/SHIFT_B: R45.2, U3.11 (SRCLK), U4.11 (SRCLK)
/SHIFT_PIN_A: J1.7, R20.1, R24.1
/SHIFT_PIN_B: J2.7, R45.1, R49.1

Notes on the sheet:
BANK A / DATA_A0 / local outputs 0,1,4,5,8,9,12,13
BANK A / DATA_A1 / local outputs 16,17,20,21,24,25,28,29
BANK B / DATA_B0 / local outputs 2,3,6,7,10,11,14,15
BANK B / DATA_B1 / local outputs 18,19,22,23,26,27,30,31
BANK A: 5V logic / separate driver supply / ARM defaults OFF
BANK B: 5V logic / separate driver supply / ARM defaults OFF

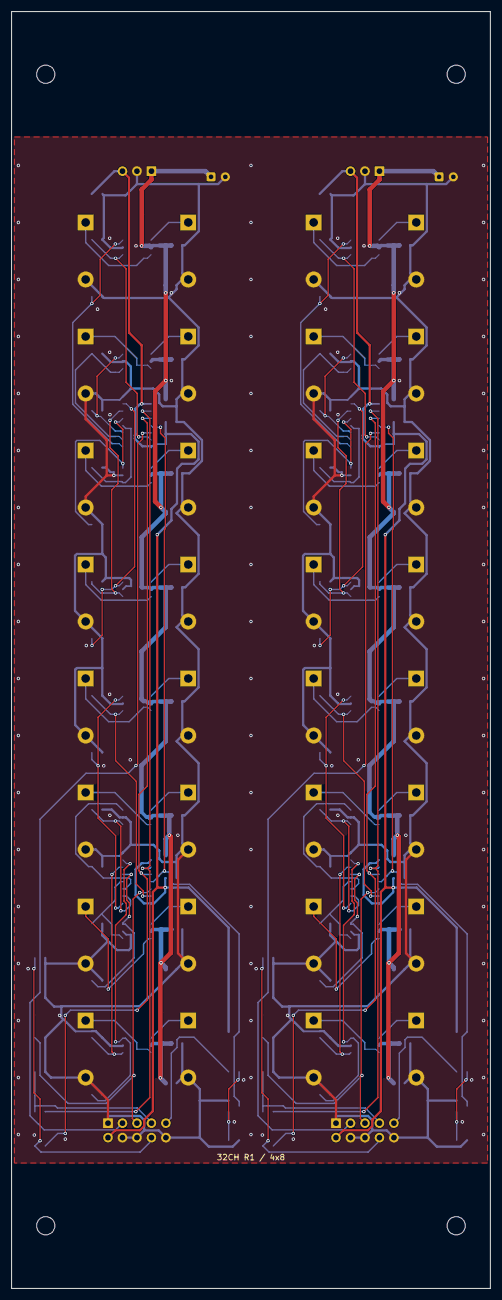
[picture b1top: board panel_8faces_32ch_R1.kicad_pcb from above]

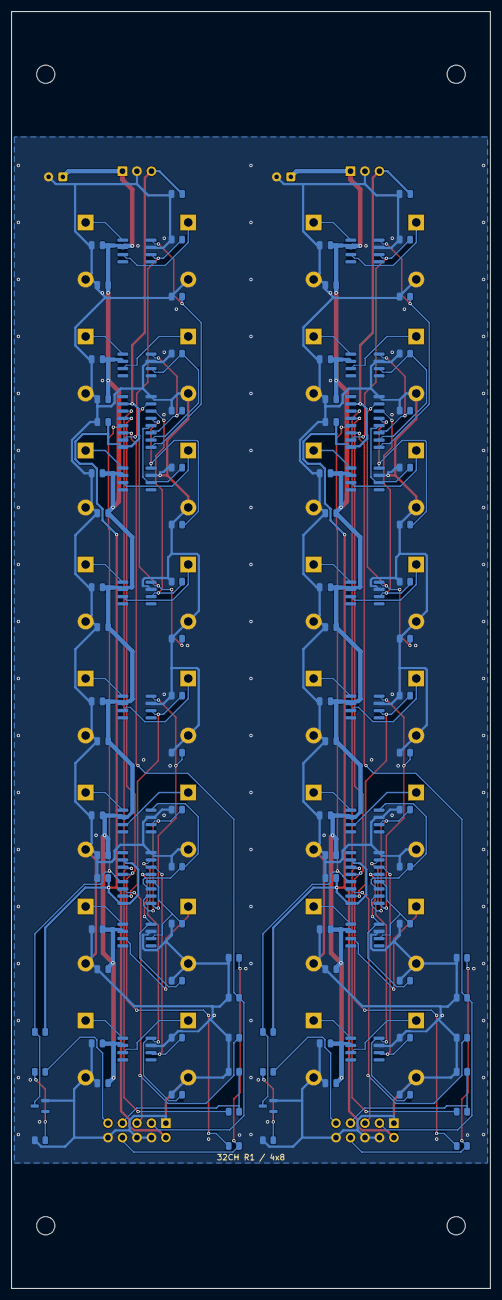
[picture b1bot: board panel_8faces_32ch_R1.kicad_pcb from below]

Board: 2 copper layers, 84.0 x 224.0 mm, 152 parts (116 on the bottom side), 87 nets.

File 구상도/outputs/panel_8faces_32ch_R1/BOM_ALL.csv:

Designator,Value,Package,Qty_per_PCB,Qty_8_PCB,Assembly,Manufacturer,MPN_candidate,LCSC_candidate,Status
"U1,U2,U3,U4",74HCT595D,SOIC-16 narrow 3.9mm,4,32,SMT,Nexperia,"74HCT595D,118",C282339,confirm exact part and availability before purchase
"U5,U6,U7,U8,U9,U10,U11,U12,U13,U14,U15,U16,U17,U18,U19,U20",TC4427A,SOIC-8,16,128,SMT,Microchip,TC4427ACOA713,C144234,confirm exact part and availability before purchase
"T1,T2,T3,T4,T5,T6,T7,T8,T9,T10,T11,T12,T13,T14,T15,T16,T17,T18,T19,T20,T21,T22,T23,T24,T25,T26,T27,T28,T29,T30,T31,T32",V40AN16T,D16mm / pin pitch 10mm,32,256,THT,,,,confirm exact part and availability before purchase
"R1,R2,R3,R4,R5,R6,R7,R8,R9,R10,R11,R12,R13,R14,R15,R16,R17,R19,R26,R27,R28,R29,R30,R31,R32,R33,R34,R35,R36,R37,R38,R39,R40,R41,R42,R44",10k,0805,36,288,SMT,YAGEO,RC0805FR-0710KL,,confirm exact part and availability before purchase
"C1,C2,C3,C4,C5,C6,C7,C8,C21,C22,C23,C24,C25,C26,C27,C28",100nF 50V,0805,16,128,SMT,YAGEO,CC0805KRX7R9BB104,C49678,confirm exact part and availability before purchase
"C11,C12,C13,C14,C15,C16,C17,C18,C31,C32,C33,C34,C35,C36,C37,C38",1uF 50V,0805,16,128,SMT,CCTC,TCC0805X7R105K500DT,C376926,confirm exact part and availability before purchase
"C9,C10,C29,C30",100nF 16V,0805,4,32,SMT,YAGEO,CC0805KRX7R9BB104,C49678,confirm exact part and availability before purchase
"C19,C39",220uF 25V,Radial D6.3mm P2.5mm,2,16,THT,Rubycon,25YXJ220M6.3X11,C88729,confirm exact part and availability before purchase
"C20,C40",10uF 16V,0805,2,16,SMT,Murata,GRM21BR61E106KA73L,,confirm exact part and availability before purchase
"Q1,Q2",MMBT3904,SOT-23,2,16,SMT,Nexperia,"MMBT3904,215",,confirm exact part and availability before purchase
"R18,R22,R23,R24,R25,R43,R47,R48,R49,R50",100k,0805,10,80,SMT,YAGEO,RC0805FR-07100KL,,confirm exact part and availability before purchase
"R20,R21,R45,R46",33R,0805,4,32,SMT,YAGEO,RC0805FR-0733RL,,confirm exact part and availability before purchase
"J1,J2",FPGA_SIGNAL_3V3,2x5 2.54mm,2,16,THT,,,,confirm exact part and availability before purchase
"J3,J4",POWER_INPUT,1x3 2.54mm,2,16,THT,,,,confirm exact part and availability before purchase
